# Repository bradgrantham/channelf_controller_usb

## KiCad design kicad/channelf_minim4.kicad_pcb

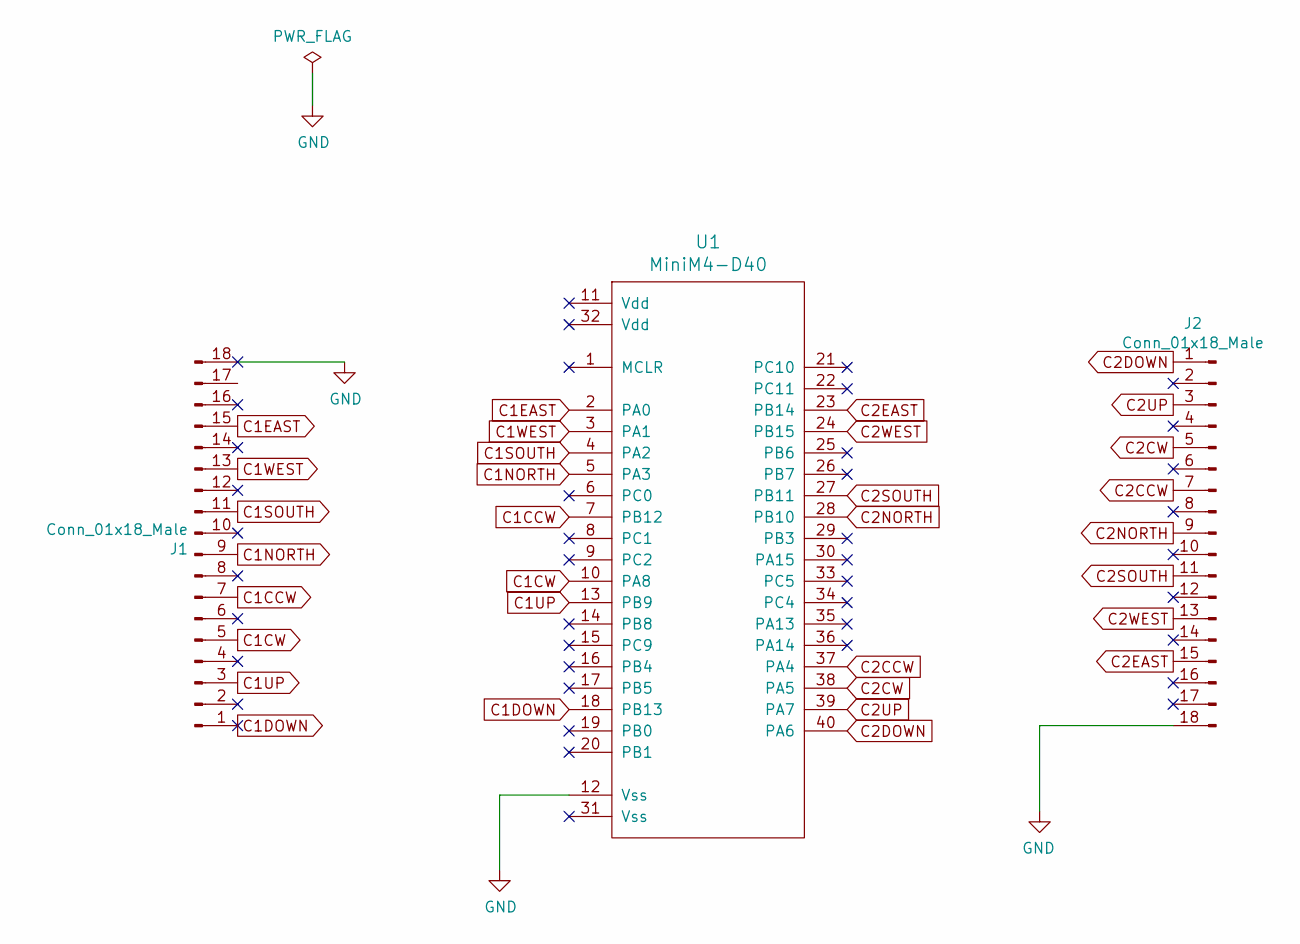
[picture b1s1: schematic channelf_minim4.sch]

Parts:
J1, J2: Conn_01x18_Male; Pin_Header_Angled_1x18_Pitch2.54mm
U1: MiniM4-D40; DIP-40_W15.24mm_Socket

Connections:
C1CCW: J1.7, U1.7 (PB12)
C1CW: J1.5, U1.10 (PA8)
C1DOWN: J1.1, U1.18 (PB13)
C1EAST: J1.15, U1.2 (PA0)
C1NORTH: J1.9, U1.5 (PA3)
C1SOUTH: J1.11, U1.4 (PA2)
C1UP: J1.3, U1.13 (PB9)
C1WEST: J1.13, U1.3 (PA1)
C2CCW: J2.7, U1.37 (PA4)
C2CW: J2.5, U1.38 (PA5)
C2DOWN: J2.1, U1.40 (PA6)
C2EAST: J2.15, U1.23 (PB14)
C2NORTH: J2.9, U1.28 (PB10)
C2SOUTH: J2.11, U1.27 (PB11)
C2UP: J2.3, U1.39 (PA7)
C2WEST: J2.13, U1.24 (PB15)
GND: J1.18, J2.18, U1.12 (Vss)

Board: 2 copper layers, 3 parts (0 on the bottom side), 17 nets, no tracks yet.

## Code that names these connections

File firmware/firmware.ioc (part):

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Mcu.Name=STM32F415RGTx
Mcu.Package=LQFP64
Mcu.UserName=STM32F415RGTx
PA0-WKUP.GPIOParameters=GPIO_PuPd,GPIO_Label
PA0-WKUP.GPIO_Label=C1EAST
PA0-WKUP.GPIO_PuPd=GPIO_PULLUP
PA0-WKUP.Signal=GPIO_Input
PA1.GPIOParameters=GPIO_PuPd,GPIO_Label
PA1.GPIO_Label=C1WEST
PA1.GPIO_PuPd=GPIO_PULLUP
PA1.Signal=GPIO_Input
PA11.Mode=Device_Only
PA11.Signal=USB_OTG_FS_DM
PA12.Mode=Device_Only
PA12.Signal=USB_OTG_FS_DP
PA2.GPIOParameters=GPIO_PuPd,GPIO_Label,GPIO_Mode
PA2.GPIO_Label=C1SOUTH
PA2.GPIO_Mode=GPIO_MODE_INPUT
PA2.GPIO_PuPd=GPIO_PULLUP
PA2.Signal=GPIO_Input
PA3.GPIOParameters=GPIO_PuPd,GPIO_Label,GPIO_Mode
PA3.GPIO_Label=C1NORTH
PA3.GPIO_Mode=GPIO_MODE_INPUT
PA3.GPIO_PuPd=GPIO_PULLUP
PA3.Signal=GPIO_Input
PA4.GPIOParameters=GPIO_PuPd,GPIO_Label,GPIO_Mode
PA4.GPIO_Label=C2CCW
PA4.GPIO_Mode=GPIO_MODE_INPUT
PA4.GPIO_PuPd=GPIO_PULLUP
PA4.Signal=GPIO_Input
PA5.GPIOParameters=GPIO_PuPd,GPIO_Label,GPIO_Mode
PA5.GPIO_Label=C2CW
PA5.GPIO_Mode=GPIO_MODE_INPUT
PA5.GPIO_PuPd=GPIO_PULLUP
PA5.Signal=GPIO_Input
PA6.GPIOParameters=GPIO_PuPd,GPIO_Label,GPIO_Mode
PA6.GPIO_Label=C2DOWN
PA6.GPIO_Mode=GPIO_MODE_INPUT
PA6.GPIO_PuPd=GPIO_PULLUP
PA6.Signal=GPIO_Input
PA7.GPIOParameters=GPIO_PuPd,GPIO_Label,GPIO_Mode
PA7.GPIO_Label=C2UP
PA7.GPIO_Mode=GPIO_MODE_INPUT
PA7.GPIO_PuPd=GPIO_PULLUP
PA7.Signal=GPIO_Input
PA8.Mode=I2C
PA8.Signal=I2C3_SCL
PB10.GPIOParameters=GPIO_PuPd,GPIO_Label,GPIO_Mode
PB10.GPIO_Label=C2NORTH
PB10.GPIO_Mode=GPIO_MODE_INPUT
PB10.GPIO_PuPd=GPIO_PULLUP
PB10.Signal=GPIO_Input
PB11.GPIOParameters=GPIO_PuPd,GPIO_Label,GPIO_Mode
PB11.GPIO_Label=C2SOUTH
PB11.GPIO_Mode=GPIO_MODE_INPUT
PB11.GPIO_PuPd=GPIO_PULLUP
PB11.Signal=GPIO_Input
PB12.GPIOParameters=GPIO_PuPd,GPIO_Label,GPIO_Mode
PB12.GPIO_Label=C1CCW
PB12.GPIO_Mode=GPIO_MODE_INPUT
PB12.GPIO_PuPd=GPIO_PULLUP
PB12.Signal=GPIO_Input
PB13.GPIOParameters=GPIO_PuPd,GPIO_Label,GPIO_Mode
PB13.GPIO_Label=C1DOWN
PB13.GPIO_Mode=GPIO_MODE_INPUT
PB13.GPIO_PuPd=GPIO_PULLUP
PB13.Signal=GPIO_Input
PB14.GPIOParameters=GPIO_PuPd,GPIO_Label,GPIO_Mode
PB14.GPIO_Label=C2EAST
PB14.GPIO_Mode=GPIO_MODE_INPUT
PB14.GPIO_PuPd=GPIO_PULLUP
PB14.Signal=GPIO_Input
PB15.GPIOParameters=GPIO_PuPd,GPIO_Label,GPIO_Mode
PB15.GPIO_Label=C2WEST
PB15.GPIO_Mode=GPIO_MODE_INPUT
PB15.GPIO_PuPd=GPIO_PULLUP
PB15.Signal=GPIO_Input
PB6.Mode=Asynchronous
PB6.Signal=USART1_TX
PB7.Mode=Asynchronous
PB7.Signal=USART1_RX
PB8.GPIOParameters=GPIO_PuPd,GPIO_Label
PB8.GPIO_Label=C1UP
PB8.GPIO_PuPd=GPIO_PULLUP
PB8.Signal=GPIO_Input
PB9.GPIOParameters=GPIO_PuPd,GPIO_Label,GPIO_Mode
PB9.GPIO_Label=C1CW
PB9.GPIO_Mode=GPIO_MODE_INPUT
PB9.GPIO_PuPd=GPIO_PULLUP
PB9.Signal=GPIO_Input
PC0.GPIOParameters=GPIO_PuPd,GPIO_Label
PC0.GPIO_Label=GAME1
PC0.GPIO_PuPd=GPIO_PULLUP
PC0.Signal=GPIO_Input
PC1.GPIOParameters=GPIO_PuPd,GPIO_Label
PC1.GPIO_Label=GAME2
PC1.GPIO_PuPd=GPIO_PULLUP
PC1.Signal=GPIO_Input
PC12.GPIOParameters=GPIO_PuPd,GPIO_Label
PC12.GPIO_Label=LED_YELLOW
PC12.GPIO_PuPd=GPIO_NOPULL
PC12.Signal=GPIO_Output
PC13-ANTI_TAMP.GPIOParameters=PinState,GPIO_PuPd,GPIO_Label
PC13-ANTI_TAMP.GPIO_Label=LED_RED
PC13-ANTI_TAMP.GPIO_PuPd=GPIO_NOPULL
PC13-ANTI_TAMP.PinState=GPIO_PIN_RESET
PC13-ANTI_TAMP.Signal=GPIO_Output
PC14-OSC32_IN.Mode=LSE-External-Oscillator
PC14-OSC32_IN.Signal=RCC_OSC32_IN
PC15-OSC32_OUT.Mode=LSE-External-Oscillator
PC15-OSC32_OUT.Signal=RCC_OSC32_OUT
PC2.GPIOParameters=GPIO_PuPd,GPIO_Label
PC2.GPIO_Label=GAME3
PC2.GPIO_PuPd=GPIO_PULLUP
PC2.Signal=GPIO_Input
PC3.GPIOParameters=GPIO_PuPd,GPIO_Label
PC3.GPIO_Label=GAME4
PC3.GPIO_PuPd=GPIO_PULLUP
PC3.Signal=GPIO_Input
PC4.GPIOParameters=GPIO_PuPd,GPIO_Label
PC4.GPIO_Label=SYSRESET
PC4.GPIO_PuPd=GPIO_PULLUP
PC4.Signal=GPIO_Input
PC9.Mode=I2C
PC9.Signal=I2C3_SDA
PH0-OSC_IN.Mode=HSE-External-Oscillator
PH0-OSC_IN.Signal=RCC_OSC_IN
PH1-OSC_OUT.Mode=HSE-External-Oscillator
PH1-OSC_OUT.Signal=RCC_OSC_OUT
RCC.HSE_VALUE=16000000
RCC.SYSCLKFreq_VALUE=168000000
RCC.SYSCLKSource=RCC_SYSCLKSOURCE_PLLCLK
board=firmware

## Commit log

2019-10-31 advertise 16 buttons, fill in 8 of them
2019-10-31 send controller 2 in upper uint16
2019-11-02 add GAME and RESET buttons and enable I2C for display
2019-11-02 add additional buttons
    Change RESET to SYSRESET to avoid name collision
    Make buttons a flat array
    Add GAME and SYSRESET buttons to sent USB data
